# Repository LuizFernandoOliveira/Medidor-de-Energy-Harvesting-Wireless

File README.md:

# Medidor de Energy Harvesting Wireless

## Descrição
O Medidor de Energy Harvesting Wireless é um circuito eletrônico dedicado a realizar a coleta de dados essenciais para aplicações técnico-científicas relacionadas a Energy Harveting via TEG, PVG, RFG, HEG, WIG, PZT e TC.

---

## Descrições técnicas

- Microcontrolador: MSP430FR5949;
- Armazenamento local via micro SD card;
- Envio de dados via UART ou via BLE 5.0;
- Medições de Geradores Termoelétricos (TEG):
  - Temperatura lado Quente;
  - Temperatura lado Frio;
  - Temperatura Ambiente;
- Medições de Geradores Fotovoltaicos (PVG):
  - Medidor de Tensão DC;
  - Medidor de Iluminação;
- Medições de Geradores via Transformadores de Corrente (TCG):
  - Medidor de Tensão AC;
- Medições de Geradores Piezoelétricos (PZT):
  - Medidor de Tensão AC;
  - Medidor de aceleração triaxial;
- Medidções de Geradores Hidroelétricos (HEG):
  - Medidor de Tensão;
  - Medidor de Corrente; 
- Medições de Geradores Eólicos (WIG):
  - Medidor de Tensão;
  - Medidor de Corrente; 
- Medições de Geradores via RF (RFG):
  - Medidor de Tensão;

---

## Estrutura do repositório
Os arquivos de hardware foram desenvolvidos utilizando o KiCad 9.0.
- **`.kicad_pcb`**: Layout da placa de circuito impresso (Board).
- **`.kicad_sch`**: Esquemático eletrônico do sistema (Schematic).
- **`.kicad_pro`**: Gerenciador de projeto do KiCad (Project).

---

## Autor
**Dr. Luiz Fernando Pinto de Oliveira**

*Engenheiro Eletrônico especializado em Sistemas Embarcados e Ultra-Low Power.*
- **Website:** [FAPLO](https://faplo.webnode.page/)
- **LinkedIn:** [lfpo](https://www.linkedin.com/in/lfpo/)

---

Shield: [![CC BY-NC-ND 4.0][cc-by-nc-nd-shield]][cc-by-nc-nd]

This work is licensed under a
[Creative Commons Attribution-NonCommercial-NoDerivs 4.0 International License][cc-by-nc-nd].

[![CC BY-NC-ND 4.0][cc-by-nc-nd-image]][cc-by-nc-nd]

[cc-by-nc-nd]: http://creativecommons.org/licenses/by-nc-nd/4.0/
[cc-by-nc-nd-image]: https://licensebuttons.net/l/by-nc-nd/4.0/88x31.png
[cc-by-nc-nd-shield]: https://img.shields.io/badge/License-CC%20BY--NC--ND%204.0-lightgrey.svg

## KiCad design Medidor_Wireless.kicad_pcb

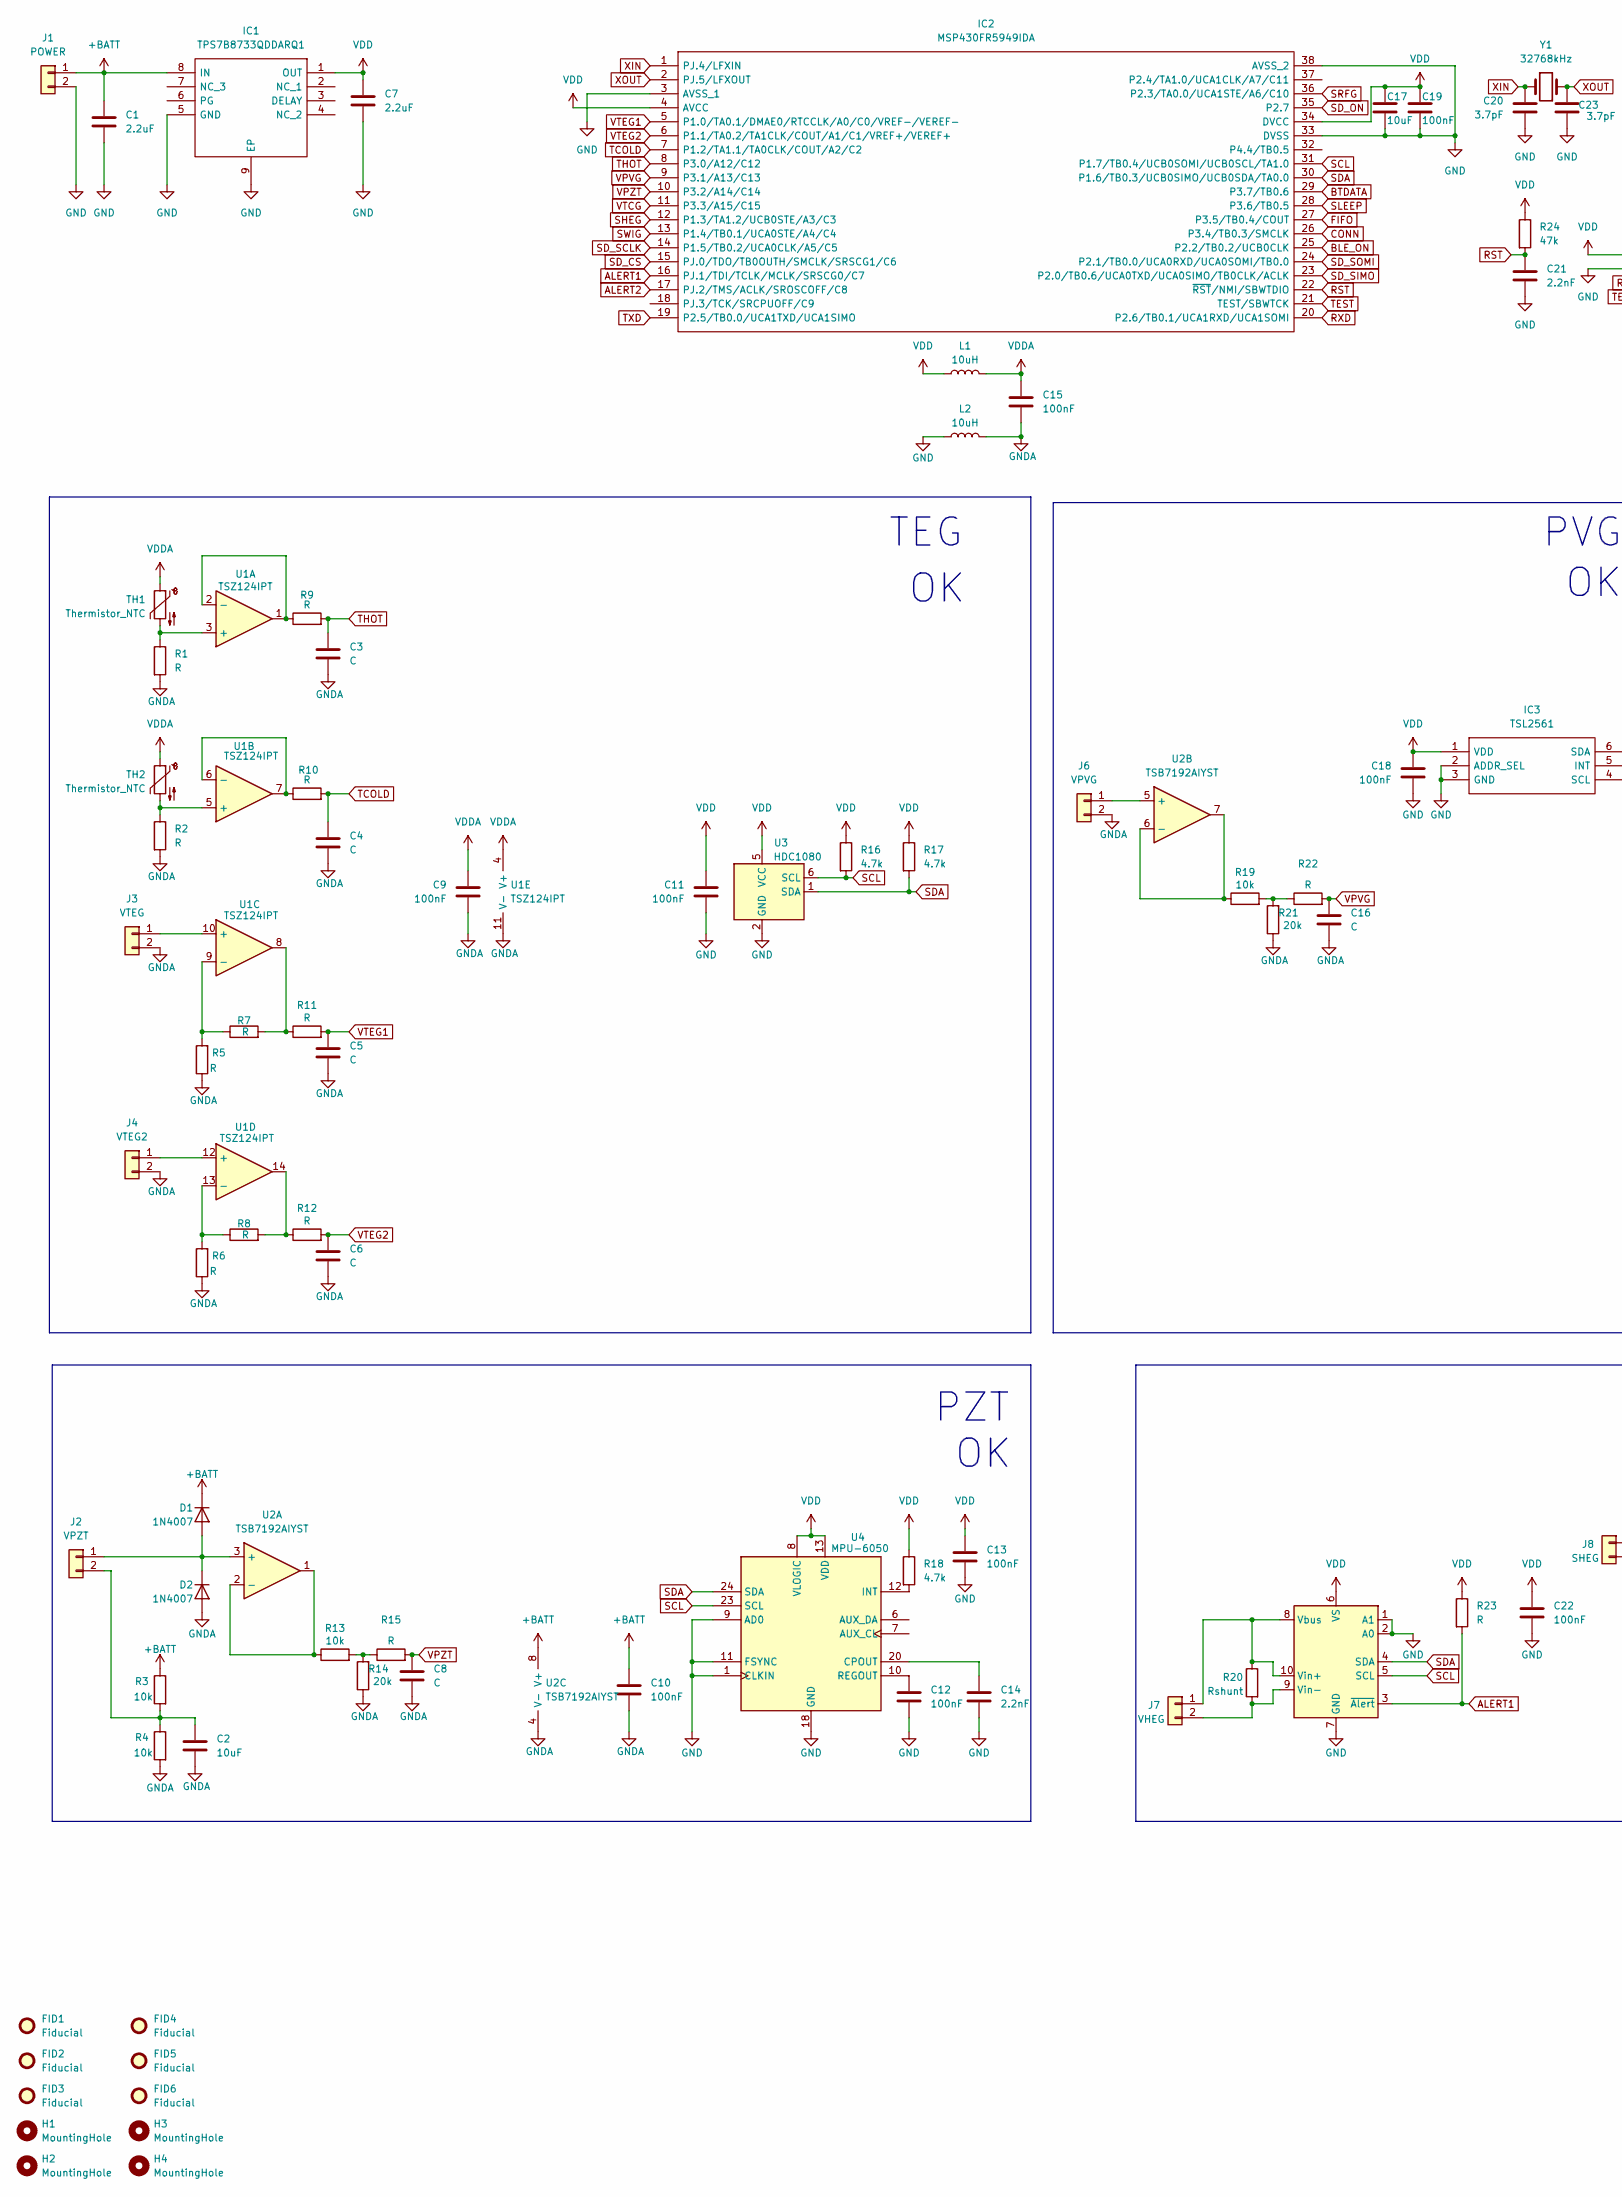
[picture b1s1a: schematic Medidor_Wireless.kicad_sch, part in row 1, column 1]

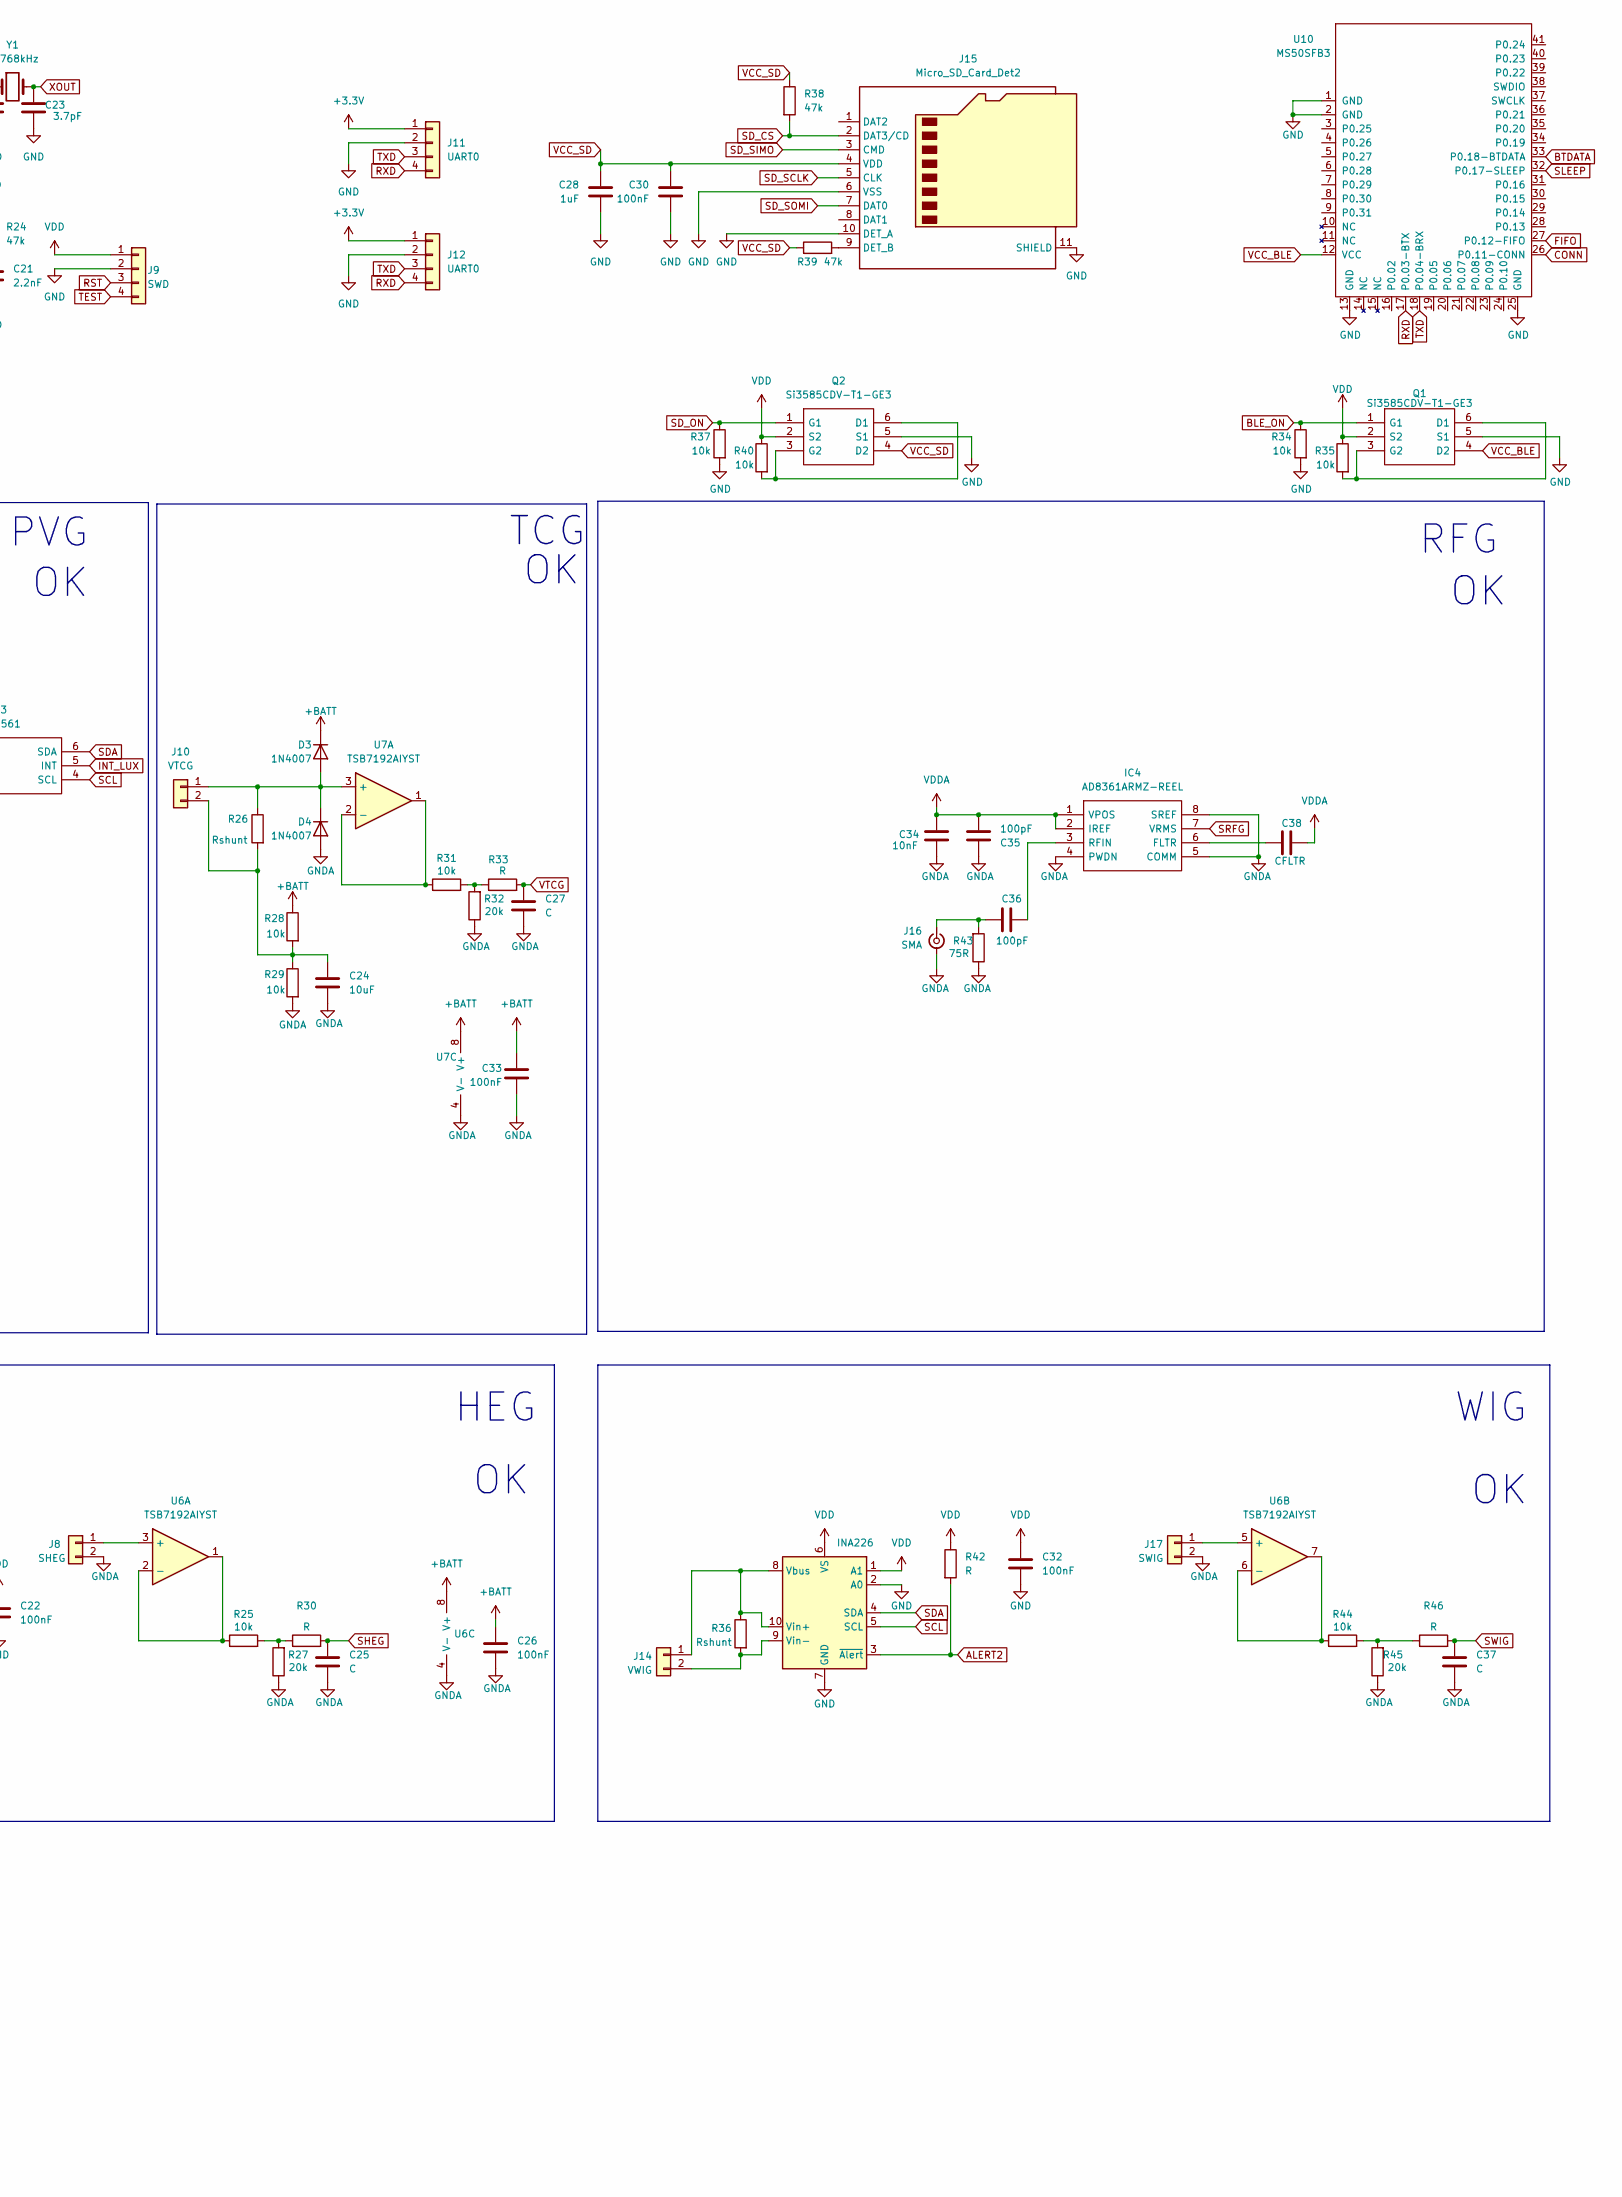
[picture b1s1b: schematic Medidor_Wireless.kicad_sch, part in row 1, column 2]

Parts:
C1, C7: 2.2uF; C_0805_2012Metric
C2, C17, C24: 10uF; C_0805_2012Metric
C3, C4, C5, C6, C8, C16, C25, C27, C37: C; C_0805_2012Metric
C9, C10, C11, C12, C13, C15, C18, C19, C22, C26, C30, C32, C33: 100nF; C_0805_2012Metric
C14, C21: 2.2nF; C_0805_2012Metric
C20, C23: 3.7pF; C_0805_2012Metric
C28: 1uF; C_0805_2012Metric
C34: 10nF; C_0805_2012Metric
C35, C36: 100pF; C_0805_2012Metric
C38: CFLTR; C_0805_2012Metric
D1, D2, D3, D4: 1N4007; D_SOD-123
FID1, FID2, FID3, FID4, FID5, FID6: Fiducial; Fiducial_1mm_Mask2mm
H1, H2, H3, H4: MountingHole; MountingHole_3.2mm_M3_DIN965
IC1: TPS7B8733QDDARQ1; SOIC127P600X170-9N; Manufacturer_Part_Number TPS7B8733QDDARQ1; Mouser Part Number 595-TPS7B8733QDDARQ1
IC2: MSP430FR5949IDA; SOP65P810X120-38N; Manufacturer_Part_Number MSP430FR5949IDA; Mouser Part Number 595-P430FR5949IDA
IC3: TSL2561; Manufacturer_Part_Number TSL2561; Mouser Part Number N/A
IC4: AD8361ARMZ-REEL; SOP65P490X110-8N; Manufacturer_Part_Number AD8361ARMZ-REEL; Mouser Part Number 584-AD8361ARMZ-R
J1: POWER; PinHeader_1x02_P2.54mm_Vertical
J2: VPZT; PinHeader_1x02_P2.54mm_Vertical
J3: VTEG; PinHeader_1x02_P2.54mm_Vertical
J4: VTEG2; PinHeader_1x02_P2.54mm_Vertical
J6: VPVG; PinHeader_1x02_P2.54mm_Vertical
J7: VHEG; PinHeader_1x02_P2.54mm_Vertical
J8: SHEG; PinHeader_1x02_P2.54mm_Vertical
J9: SWD; PinHeader_1x04_P1.27mm_Vertical
J10: VTCG; PinHeader_1x02_P2.54mm_Vertical
J11: UART0; PinHeader_1x04_P2.54mm_Vertical
J12: UART0; JST_XH_S4B-XH-A_1x04_P2.50mm_Horizontal
J14: VWIG; PinHeader_1x02_P2.54mm_Vertical
J15: Micro_SD_Card_Det2; microSD_HC_Hirose_DM3AT-SF-PEJM5
J16: SMA; SMA_Amphenol_132289_EdgeMount
J17: SWIG; PinHeader_1x02_P2.54mm_Vertical
L1, L2: 10uH; L_0805_2012Metric
Q1, Q2: Si3585CDV-T1-GE3; SOT95P284X110-6N; Manufacturer_Part_Number Si3585CDV-T1-GE3; Mouser Part Number 78-SI3585CDV-T1-GE3
R1, R2, R5, R6, R7, R8, R9, R10, R11, R12, R15, R22, R23, R30, R33, R42, R46: R; R_0805_2012Metric
R3, R4, R13, R19, R25, R28, R29, R31, R34, R35, R37, R40, R44: 10k; R_0805_2012Metric
R14, R21, R27, R32, R45: 20k; R_0805_2012Metric
R16, R17, R18: 4.7k; R_0805_2012Metric
R20, R36: Rshunt; R_1206_3216Metric
R24, R38, R39: 47k; R_0805_2012Metric
R26: Rshunt; R_0805_2012Metric
R43: 75R; R_0805_2012Metric
TH1, TH2: Thermistor_NTC; PinHeader_1x02_P2.54mm_Vertical
U1: TSZ124IPT; SOP65P640X120-14N
U2, U6, U7: TSB7192AIYST; SOP65P490X110-8N
U3: HDC1080; Texas_PWSON-N6
U4: MPU-6050; InvenSense_QFN-24_4x4mm_P0.5mm
U5, U9: INA226; VSSOP-10_3x3mm_P0.5mm
U10: MS50SFB3
Y1: 32768kHz; D_0805_2012Metric

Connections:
+3.3V: J11.1, J12.1
+BATT: C1.1, C10.1, C26.1, C33.1, D1.1 (K), D3.1 (K), IC1.8 (IN), J1.1, R3.1, R28.1, U2.8 (V+), U6.8 (V+), U7.8 (V+)
ALERT1: IC2.16 (PJ.1/TDI/TCLK/MCLK/SRSCG0/C7), R23.2, U5.3 (~Alert)
ALERT2: IC2.17 (PJ.2/TMS/ACLK/SROSCOFF/C8), R42.2, U9.3 (~Alert)
BLE_ON: IC2.25 (P2.2/TB0.2/UCB0CLK), Q1.1 (G1), R34.1
BTDATA: IC2.29 (P3.7/TB0.6), U10.33 (P0.18-BTDATA)
CONN: IC2.26 (P3.4/TB0.3/SMCLK), U10.26 (P0.11-CONN)
FIFO: IC2.27 (P3.5/TB0.4/COUT), U10.27 (P0.12-FIFO)
GND: C1.2, C7.2, C11.2, C12.2, C13.2, C14.2, C17.2, C18.2, C19.2, C20.2, C21.2, C22.2, C23.2, C28.2, C30.2, C32.2, IC1.5 (GND), IC1.9 (EP), IC2.3 (AVSS_1), IC2.33 (DVSS), IC2.38 (AVSS_2), IC3.2 (ADDR_SEL), IC3.3 (GND), J1.2, J9.2, J11.2, J12.2, J15.6 (VSS), J15.10 (DET_A), J15.11 (SHIELD), L2.1, Q1.5 (S1), Q2.5 (S1), R34.2, R37.2, U3.2 (GND), U4.1 (CLKIN), U4.9 (AD0), U4.11 (FSYNC), U4.18 (GND), U5.1 (A1), U5.2 (A0), U5.7 (GND), U9.2 (A0), U9.7 (GND), U10.1 (GND), U10.2 (GND), U10.13 (GND), U10.25 (GND)
GNDA: C2.2, C3.2, C4.2, C5.2, C6.2, C8.2, C9.2, C10.2, C15.2, C16.2, C24.2, C25.2, C26.2, C27.2, C33.2, C34.1, C35.1, C37.2, D2.2 (A), D4.2 (A), IC4.4 (PWDN), IC4.5 (COMM), IC4.8 (SREF), J3.2, J4.2, J6.2, J8.2, J16.2 (Ext), J17.2, L2.2, R1.2, R2.2, R4.2, R5.1, R6.1, R14.1, R21.1, R27.1, R29.2, R32.1, R43.1, R45.1, U1.11 (V-), U2.4 (V-), U6.4 (V-), U7.4 (V-)
INT_LUX: IC3.5 (INT)
unnamed: D1.2 (A), D2.1 (K), J2.1, U2.3 (+)
unnamed: D3.2 (A), D4.1 (K), J10.1, R26.1, U7.3 (+)
unnamed: C38.2, IC4.6 (FLTR)
unnamed: C36.1, IC4.3 (RFIN)
unnamed: C2.1, J2.2, R3.2, R4.1
unnamed: J3.1, U1.10 (+)
unnamed: J4.1, U1.12 (+)
unnamed: J6.1, U2.5 (+)
unnamed: J7.1, R20.1, U5.8 (Vbus), U5.10 (Vin+)
unnamed: J7.2, R20.2, U5.9 (Vin-)
unnamed: J8.1, U6.3 (+)
unnamed: C24.1, J10.2, R26.2, R28.2, R29.1
unnamed: J14.1, R36.1, U9.8 (Vbus), U9.10 (Vin+)
unnamed: J14.2, R36.2, U9.9 (Vin-)
unnamed: J15.9 (DET_B), R39.2
unnamed: C36.2, J16.1 (In), R43.2
unnamed: J17.1, U6.5 (+)
unnamed: Q1.3 (G2), Q1.6 (D1), R35.2
unnamed: Q2.3 (G2), Q2.6 (D1), R40.2
unnamed: R7.2, R11.1, U1.8
unnamed: R8.2, R12.1, U1.14
unnamed: R13.2, R14.2, R15.1
unnamed: R19.2, R21.2, R22.1
unnamed: R25.2, R27.2, R30.1
unnamed: R31.2, R32.2, R33.1
unnamed: R44.2, R45.2, R46.1
unnamed: R1.1, TH1.2, U1.3 (+)
unnamed: R9.1, U1.1, U1.2 (-)
unnamed: R2.1, TH2.2, U1.5 (+)
unnamed: R10.1, U1.6 (-), U1.7
unnamed: R5.2, R7.1, U1.9 (-)
unnamed: R6.2, R8.1, U1.13 (-)
unnamed: R13.1, U2.1, U2.2 (-)
unnamed: R19.1, U2.6 (-), U2.7
unnamed: C14.1, U4.20 (CPOUT)
unnamed: R18.2, U4.12 (INT)
unnamed: C12.1, U4.10 (REGOUT)
unnamed: R25.1, U6.1, U6.2 (-)
unnamed: R44.1, U6.6 (-), U6.7
unnamed: R31.1, U7.1, U7.2 (-)
RST: C21.1, IC2.22 (~RST/NMI/SBWTDIO), J9.3, R24.2
RXD: IC2.20 (P2.6/TB0.1/UCA1RXD/UCA1SOMI), J11.4, J12.4, U10.17 (P0.03-BTX)
SCL: IC2.31 (P1.7/TB0.4/UCB0SOMI/UCB0SCL/TA1.0), IC3.4 (SCL), R16.2, U3.6 (SCL), U4.23 (SCL), U5.5 (SCL), U9.5 (SCL)
SDA: IC2.30 (P1.6/TB0.3/UCB0SIMO/UCB0SDA/TA0.0), IC3.6 (SDA), R17.2, U3.1 (SDA), U4.24 (SDA), U5.4 (SDA), U9.4 (SDA)
SD_CS: IC2.15 (PJ.0/TDO/TB0OUTH/SMCLK/SRSCG1/C6), J15.2 (DAT3/CD), R38.2
SD_ON: IC2.35 (P2.7), Q2.1 (G1), R37.1
SD_SCLK: IC2.14 (P1.5/TB0.2/UCA0CLK/A5/C5), J15.5 (CLK)
SD_SIMO: IC2.23 (P2.0/TB0.6/UCA0TXD/UCA0SIMO/TB0CLK/ACLK), J15.3 (CMD)
SD_SOMI: IC2.24 (P2.1/TB0.0/UCA0RXD/UCA0SOMI/TB0.0), J15.7 (DAT0)
SHEG: C25.1, IC2.12 (P1.3/TA1.2/UCB0STE/A3/C3), R30.2
SLEEP: IC2.28 (P3.6/TB0.5), U10.32 (P0.17-SLEEP)
SRFG: IC2.36 (P2.3/TA0.0/UCA1STE/A6/C10), IC4.7 (VRMS)
SWIG: C37.1, IC2.13 (P1.4/TB0.1/UCA0STE/A4/C4), R46.2
TCOLD: C4.1, IC2.7 (P1.2/TA1.1/TA0CLK/COUT/A2/C2), R10.2
TEST: IC2.21 (TEST/SBWTCK), J9.4
THOT: C3.1, IC2.8 (P3.0/A12/C12), R9.2
TXD: IC2.19 (P2.5/TB0.0/UCA1TXD/UCA1SIMO), J11.3, J12.3, U10.18 (P0.04-BRX)
VCC_BLE: Q1.4 (D2), U10.12 (VCC)
VCC_SD: C28.1, C30.1, J15.4 (VDD), Q2.4 (D2), R38.1, R39.1
VDD: C7.1, C11.1, C13.1, C17.1, C18.1, C19.1, C22.1, C32.1, IC1.1 (OUT), IC2.4 (AVCC), IC2.34 (DVCC), IC3.1 (VDD), J9.1, L1.1, Q1.2 (S2), Q2.2 (S2), R16.1, R17.1, R18.1, R23.1, R24.1, R35.1, R40.1, R42.1, U3.5 (VCC), U4.8 (VLOGIC), U4.13 (VDD), U5.6 (VS), U9.1 (A1), U9.6 (VS)
VDDA: C9.1, C15.1, C34.2, C35.2, C38.1, IC4.1 (VPOS), IC4.2 (IREF), L1.2, TH1.1, TH2.1, U1.4 (V+)
VPVG: C16.1, IC2.9 (P3.1/A13/C13), R22.2
VPZT: C8.1, IC2.10 (P3.2/A14/C14), R15.2
VTCG: C27.1, IC2.11 (P3.3/A15/C15), R33.2
VTEG1: C5.1, IC2.5 (P1.0/TA0.1/DMAE0/RTCCLK/A0/C0/VREF-/VER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), R11.2
VTEG2: C6.1, IC2.6 (P1.1/TA0.2/TA1CLK/COUT/A1/C1/VREF+/VERE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), R12.2
XIN: C20.1, IC2.1 (PJ.4/LFXIN), Y1.1
XOUT: C23.1, IC2.2 (PJ.5/LFXOUT), Y1.2

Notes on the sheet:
WIG
TCG
TEG
PVG
RFG
HEG
PZT

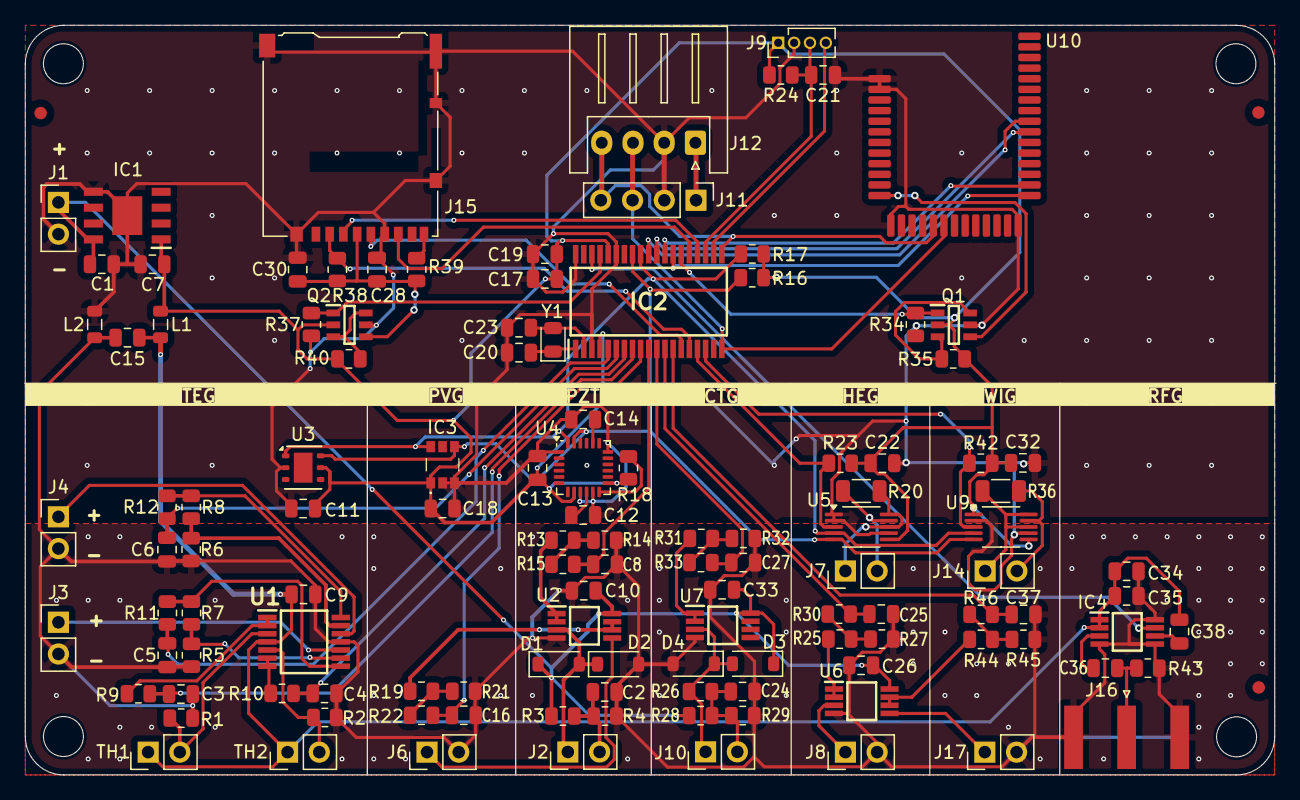
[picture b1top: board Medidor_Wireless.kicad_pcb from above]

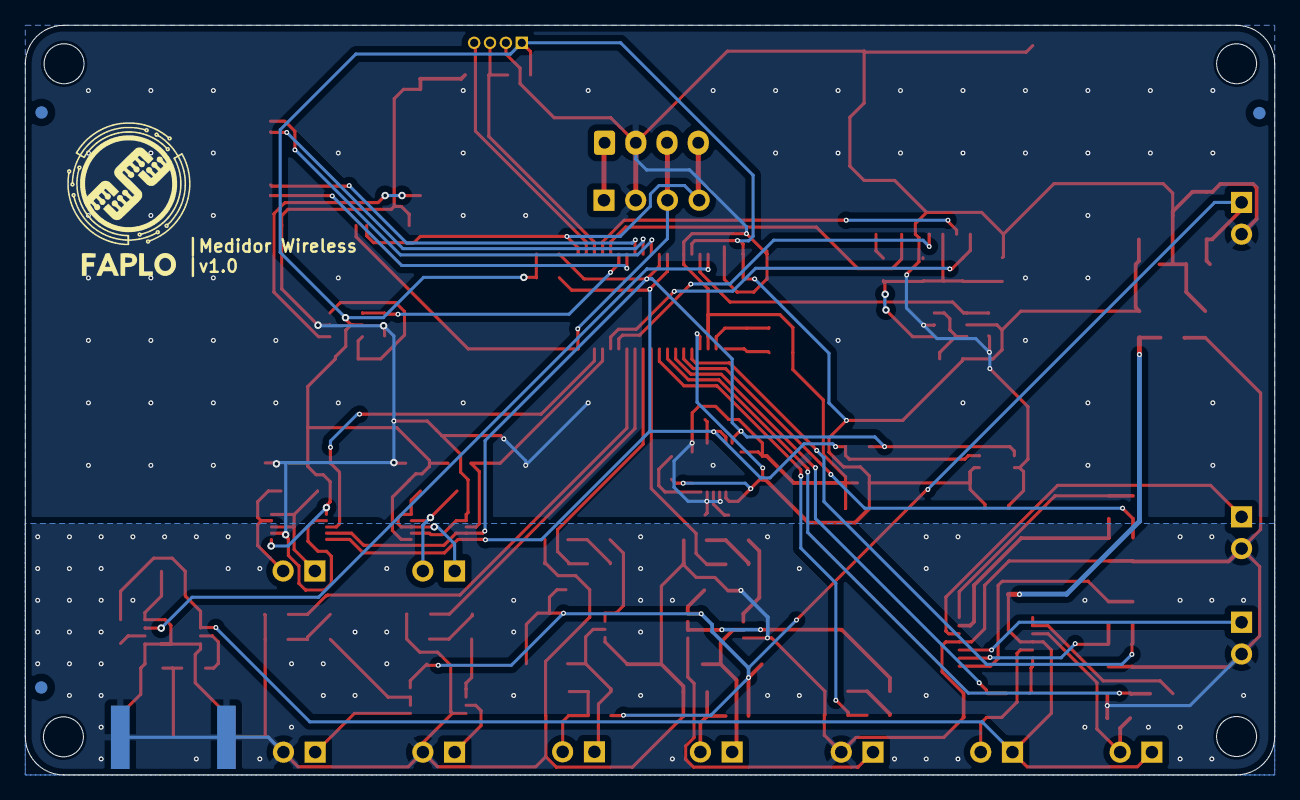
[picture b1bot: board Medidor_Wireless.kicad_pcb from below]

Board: 2 copper layers, 100.0 x 60.0 mm, 130 parts (3 on the bottom side), 78 nets.

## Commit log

2026-04-17 Inicialização do repositório
2026-04-17 Enhance README with project details and badges
    Added project status badges, detailed technical descriptions, repository structure, and author information to the README.
2026-04-17 Add LICENSE file with Creative Commons license
    Added Creative Commons Attribution-NonCommercial-NoDerivatives 4.0 International Public License to the project.
